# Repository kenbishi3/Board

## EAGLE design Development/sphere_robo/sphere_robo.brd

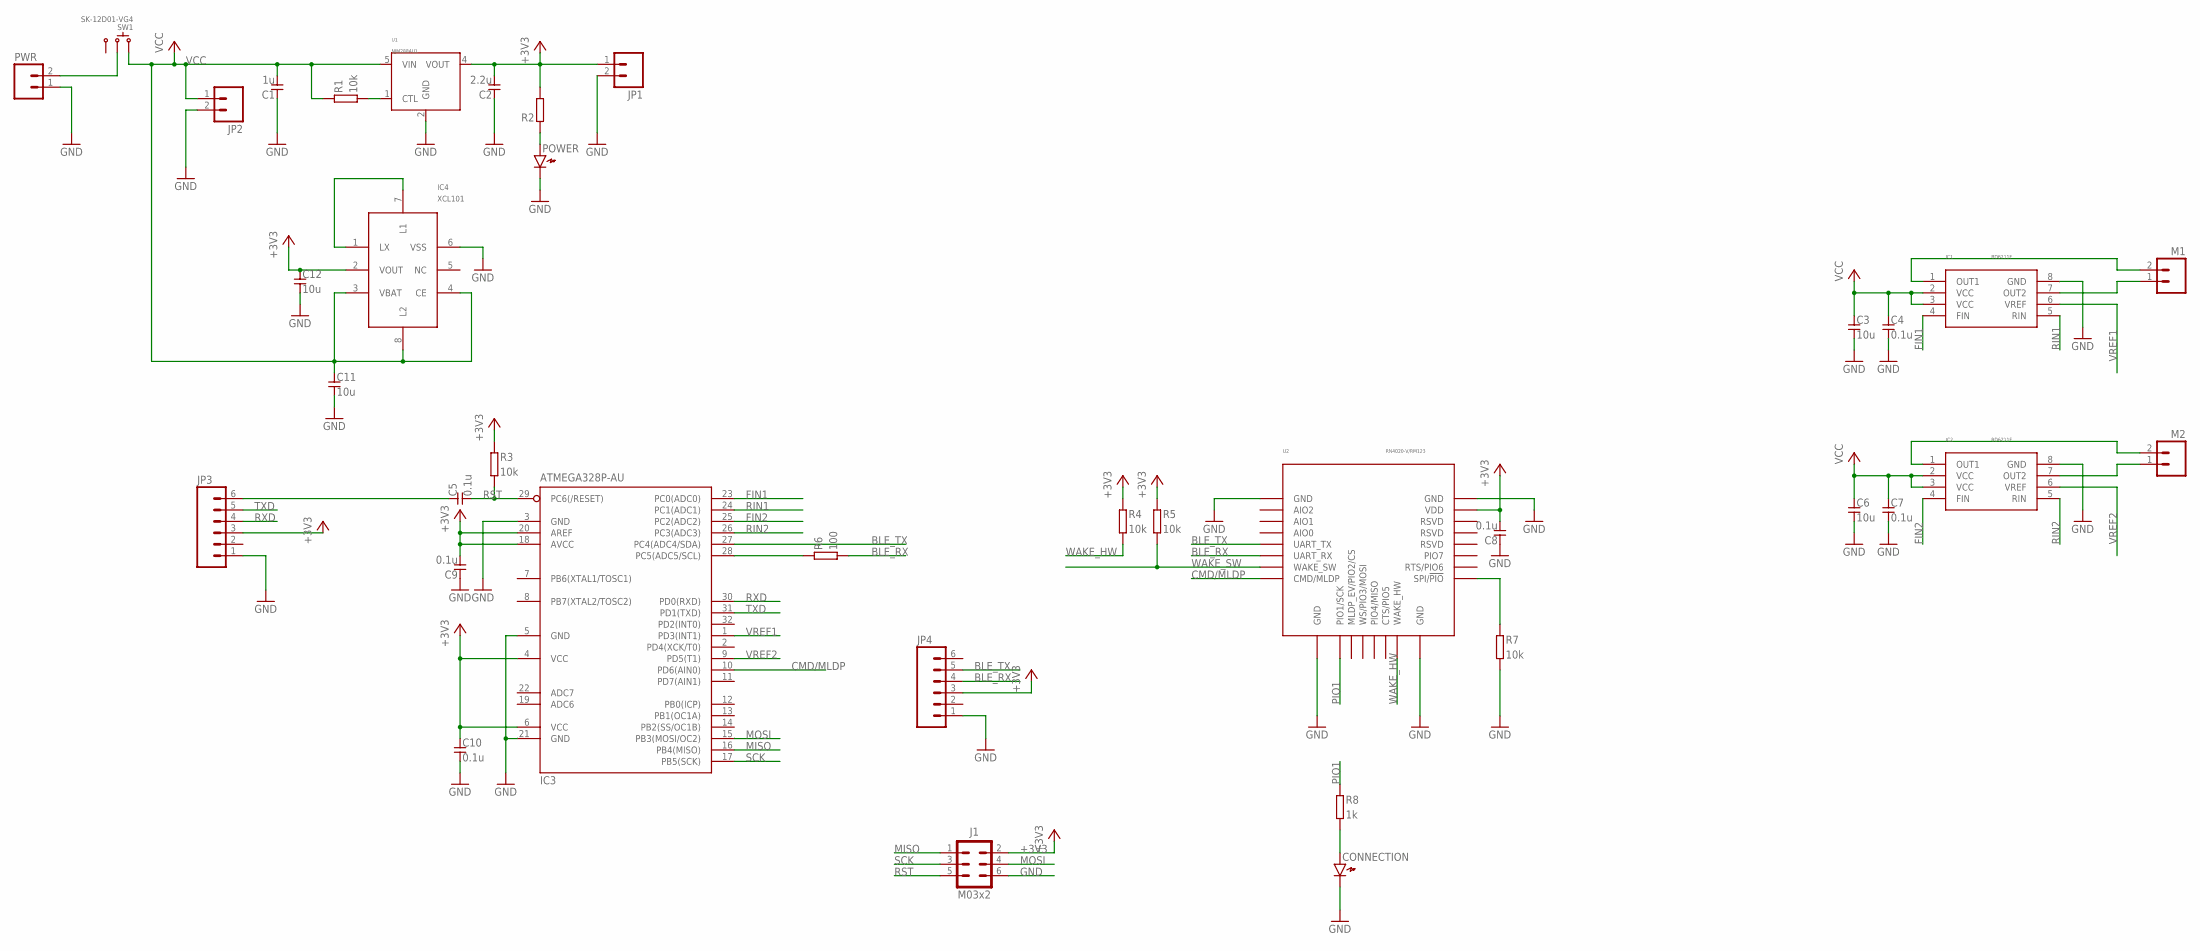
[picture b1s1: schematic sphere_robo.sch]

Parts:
C1: 1u; SMD1608_REDUCED
C2: 2.2u; SMD1608_REDUCED
C3, C6, C11, C12: 10u; SMD2012_REDUCED
C4, C5, C7, C8, C9, C10: 0.1u; SMD1608_REDUCED
CONNECTION: LED1608_REDUCED
IC1, IC2: BD6211F; SOP-8
IC3: ATMEGA328P-AU; TQFP32-08
IC4: XCL101; CL-2025
J1: M03X2STD; 2X03
JP1, JP2: M02NOSILK; 1X02-NOSILK
JP3, JP4: M06NOSILK; 1X06-NOSILK
M1, M2: M02NOSILK; 1X02-NOSILK
POWER: LED1608_REDUCED
PWR: M02NOSILK; 1X02-NOSILK
R1, R3, R4, R5, R7: 10k; SMD1608_REDUCED
R2: RESISTOR1608_REDUCED; SMD1608_REDUCED
R6: 100; SMD1608_REDUCED
R8: 1k; SMD1608_REDUCED
SW1: SK-12D01-VG4
U1: NJM2884U1; SOT-89-5
U2: RN4020-V/RM123; RN4020

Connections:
+3V3: C2.2, C8.2, C9.2, C10.1, C12.1, IC3.4 (VCC), IC3.6 (VCC), IC3.18 (AVCC), IC3.20 (AREF), IC4.2 (VOUT), J1.2, JP1.1, JP3.3, JP4.3, R2.2, R3.1, R4.1, R5.1, U1.4 (VOUT), U2.23 (VDD)
BLE_RX: JP4.4, R6.2, U2.6 (UART_RX)
BLE_TX: IC3.27 (PC4(ADC4/SDA)), JP4.5, U2.5 (UART_TX)
CMD/MLDP: IC3.10 (PD6(AIN0)), U2.8 (CMD/MLDP)
FIN1: IC1.4 (FIN), IC3.23 (PC0(ADC0))
FIN2: IC2.4 (FIN), IC3.25 (PC2(ADC2))
GND: C1.1, C2.1, C3.2, C4.2, C6.2, C7.2, C8.1, C9.1, C10.2, C11.2, C12.2, CONNECTION.K, IC1.8 (GND), IC2.8 (GND), IC3.3 (GND), IC3.5 (GND), IC3.21 (GND), IC4.6 (VSS), J1.6, JP1.2, JP2.2, JP3.1, JP4.1, POWER.K, PWR.1, R7.2, U1.2 (GND), U2.1 (GND), U2.9 (GND), U2.16 (GND), U2.24 (GND)
MISO: IC3.16 (PB4(MISO)), J1.1
MOSI: IC3.15 (PB3(MOSI/OC2)), J1.4
unnamed: C5.1, JP3.6
unnamed: CONNECTION.A, R8.2
unnamed: IC3.28 (PC5(ADC5/SCL)), R6.1
unnamed: R7.1, U2.17 (SPI/!PIO)
unnamed: PWR.2, SW1.2
unnamed: R1.2, U1.1 (CTL)
unnamed: IC4.1 (LX), IC4.7 (L1)
unnamed: POWER.A, R2.1
unnamed: IC2.1 (OUT1), M2.2
unnamed: IC2.7 (OUT2), M2.1
unnamed: IC1.1 (OUT1), M1.2
unnamed: IC1.7 (OUT2), M1.1
PIO1: R8.1, U2.10 (PIO1/SCK)
RIN1: IC1.5 (RIN), IC3.24 (PC1(ADC1))
RIN2: IC2.5 (RIN), IC3.26 (PC3(ADC3))
RST: C5.2, IC3.29 (PC6(/RESET)), J1.5, R3.2
RXD: IC3.30 (PD0(RXD)), JP3.4
SCK: IC3.17 (PB5(SCK)), J1.3
TXD: IC3.31 (PD1(TXD)), JP3.5
VCC: C1.2, C3.1, C4.1, C6.1, C7.1, C11.1, IC1.2 (VCC), IC1.3 (VCC), IC2.2 (VCC), IC2.3 (VCC), IC4.3 (VBAT), IC4.4 (CE), IC4.8 (L2), JP2.1, R1.1, SW1.1, U1.5 (VIN)
VREF1: IC1.6 (VREF), IC3.1 (PD3(INT1))
VREF2: IC2.6 (VREF), IC3.9 (PD5(T1))
WAKE_HW: R4.2, U2.15 (WAKE_HW)
WAKE_SW: R5.2, U2.7 (WAKE_SW)

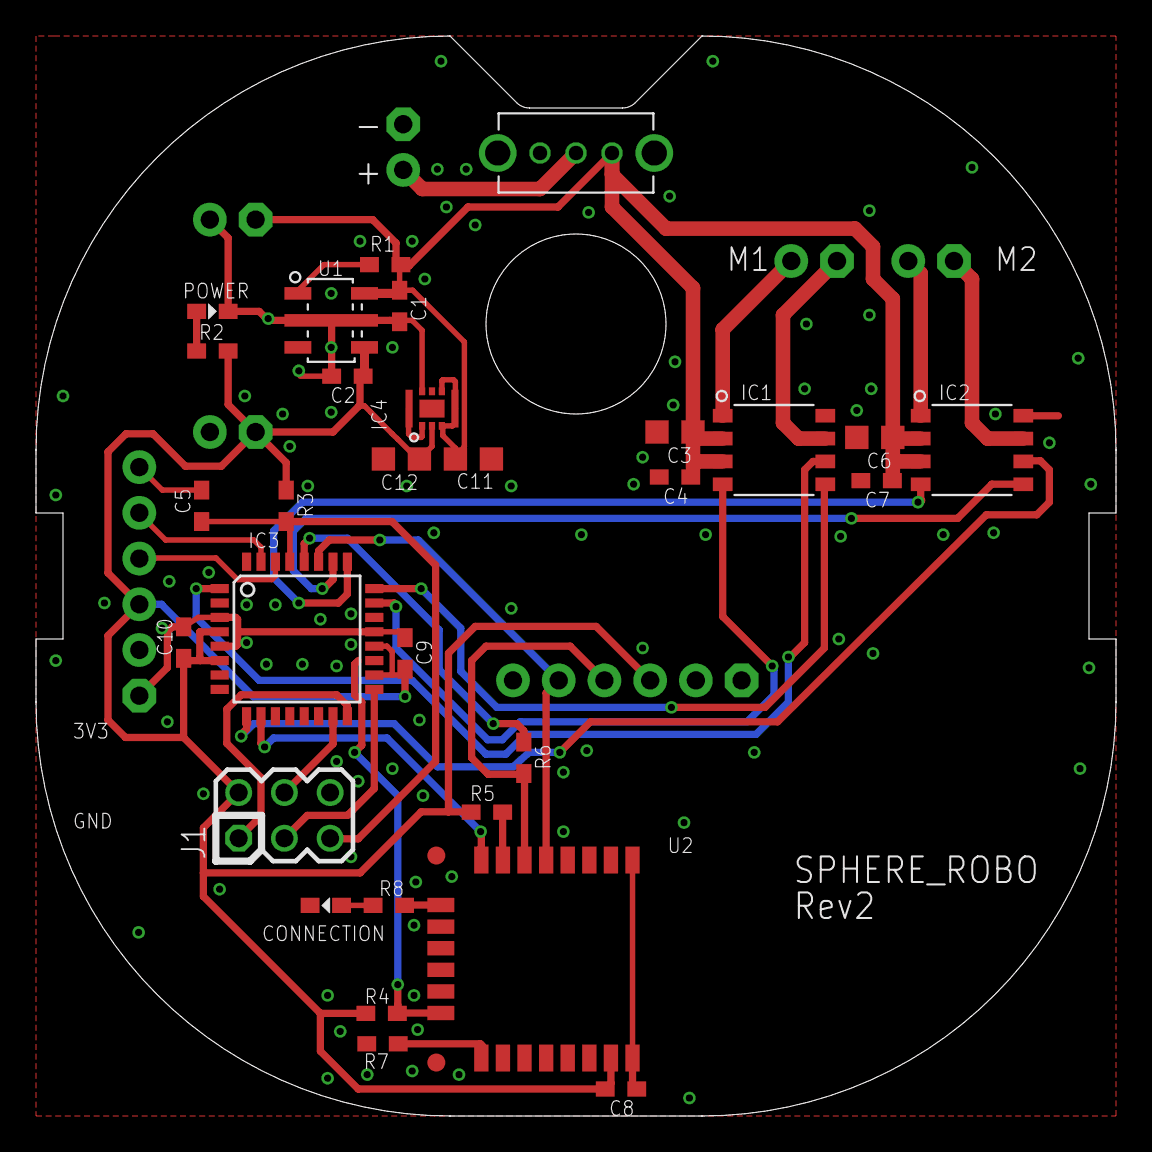
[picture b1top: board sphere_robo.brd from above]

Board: 2 copper layers, 60.0 x 60.0 mm, 37 parts (0 on the bottom side), 33 nets.

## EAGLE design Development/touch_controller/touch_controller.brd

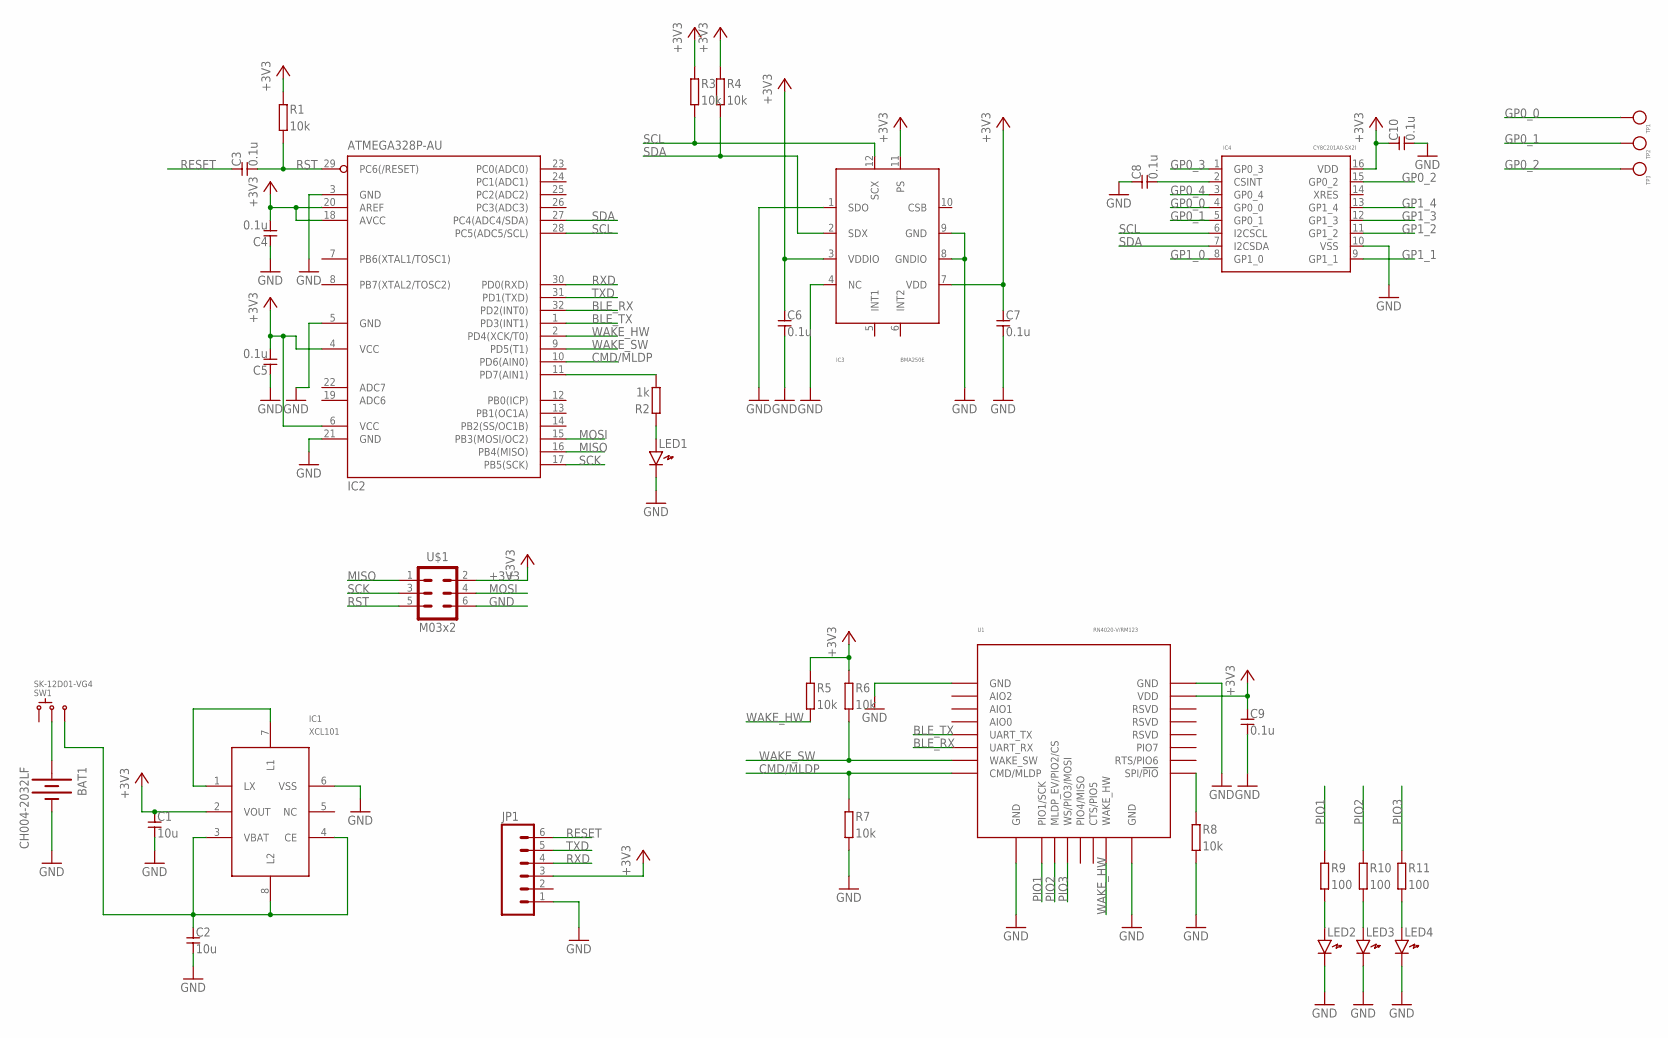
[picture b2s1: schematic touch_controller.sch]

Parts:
BAT1: CH004-2032LF
C1, C2: 10u; SMD2012_REDUCED
C3, C4, C5, C6, C7, C8, C9, C10: 0.1u; SMD1608_REDUCED
IC1: XCL101; CL-2025
IC2: ATMEGA328P-AU; TQFP32-08
IC3: BMA250E; LGA-12
IC4: CY8C201A0-SX2I; SOIC-16
JP1: M06NOSILK; 1X06-NOSILK
LED1, LED2, LED3, LED4: LED1608_REDUCED
R1, R3, R4, R5, R6, R7, R8: 10k; SMD1608_REDUCED
R2: 1k; SMD1608_REDUCED
R9, R10, R11: 100; SMD1608_REDUCED
SW1: SK-12D01-VG4
TP1, TP2, TP3: HT-0720-10
U1: RN4020-V/RM123; RN4020
U$1: M03X2STD; 2X03

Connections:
+3V3: C1.1, C4.2, C5.2, C6.1, C7.1, C9.1, C10.1, IC1.2 (VOUT), IC2.4 (VCC), IC2.6 (VCC), IC2.18 (AVCC), IC2.20 (AREF), IC3.3 (VDDIO), IC3.7 (VDD), IC3.11 (PS), IC4.16 (VDD), JP1.3, R1.1, R3.1, R4.1, R5.1, R6.1, U1.23 (VDD), U$1.2
BLE_RX: IC2.32 (PD2(INT0)), U1.6 (UART_RX)
BLE_TX: IC2.1 (PD3(INT1)), U1.5 (UART_TX)
CMD/MLDP: IC2.10 (PD6(AIN0)), R7.1, U1.8 (CMD/MLDP)
GND: BAT1.-, C1.2, C2.2, C4.1, C5.1, C6.2, C7.2, C8.1, C9.2, C10.2, IC1.6 (VSS), IC2.3 (GND), IC2.5 (GND), IC2.21 (GND), IC3.1 (SDO), IC3.4 (NC), IC3.8 (GNDIO), IC3.9 (GND), IC4.10 (VSS), JP1.1, LED1.K, LED2.K, LED3.K, LED4.K, R7.2, R8.2, U1.1 (GND), U1.9 (GND), U1.16 (GND), U1.24 (GND), U$1.6
GP0_0: IC4.4 (GP0_0), TP1.P$1
GP0_1: IC4.5 (GP0_1), TP2.P$1
GP0_2: IC4.15 (GP0_2), TP3.P$1
GP0_3: IC4.1 (GP0_3)
GP0_4: IC4.3 (GP0_4)
GP1_0: IC4.8 (GP1_0)
GP1_1: IC4.9 (GP1_1)
GP1_2: IC4.11 (GP1_2)
GP1_3: IC4.12 (GP1_3)
GP1_4: IC4.13 (GP1_4)
MISO: IC2.16 (PB4(MISO)), U$1.1
MOSI: IC2.15 (PB3(MOSI/OC2)), U$1.4
unnamed: BAT1.+, SW1.2
unnamed: C8.2, IC4.2 (CSINT)
unnamed: R8.1, U1.17 (SPI/!PIO)
unnamed: IC2.11 (PD7(AIN1)), R2.2
unnamed: LED2.A, R9.2
unnamed: LED3.A, R10.2
unnamed: LED4.A, R11.2
unnamed: LED1.A, R2.1
unnamed: C2.1, IC1.3 (VBAT), IC1.4 (CE), IC1.8 (L2), SW1.3
unnamed: IC1.1 (LX), IC1.7 (L1)
PIO1: R9.1, U1.10 (PIO1/SCK)
PIO2: R10.1, U1.11 (MLDP_EV/PIO2/CS)
PIO3: R11.1, U1.12 (WS/PIO3/MOSI)
RESET: C3.1, JP1.6
RST: C3.2, IC2.29 (PC6(/RESET)), R1.2, U$1.5
RXD: IC2.30 (PD0(RXD)), JP1.4
SCK: IC2.17 (PB5(SCK)), U$1.3
SCL: IC2.28 (PC5(ADC5/SCL)), IC3.12 (SCX), IC4.6 (I2CSCL), R3.2
SDA: IC2.27 (PC4(ADC4/SDA)), IC3.2 (SDX), IC4.7 (I2CSDA), R4.2
TXD: IC2.31 (PD1(TXD)), JP1.5
WAKE_HW: IC2.2 (PD4(XCK/T0)), R5.2, U1.15 (WAKE_HW)
WAKE_SW: IC2.9 (PD5(T1)), R6.2, U1.7 (WAKE_SW)

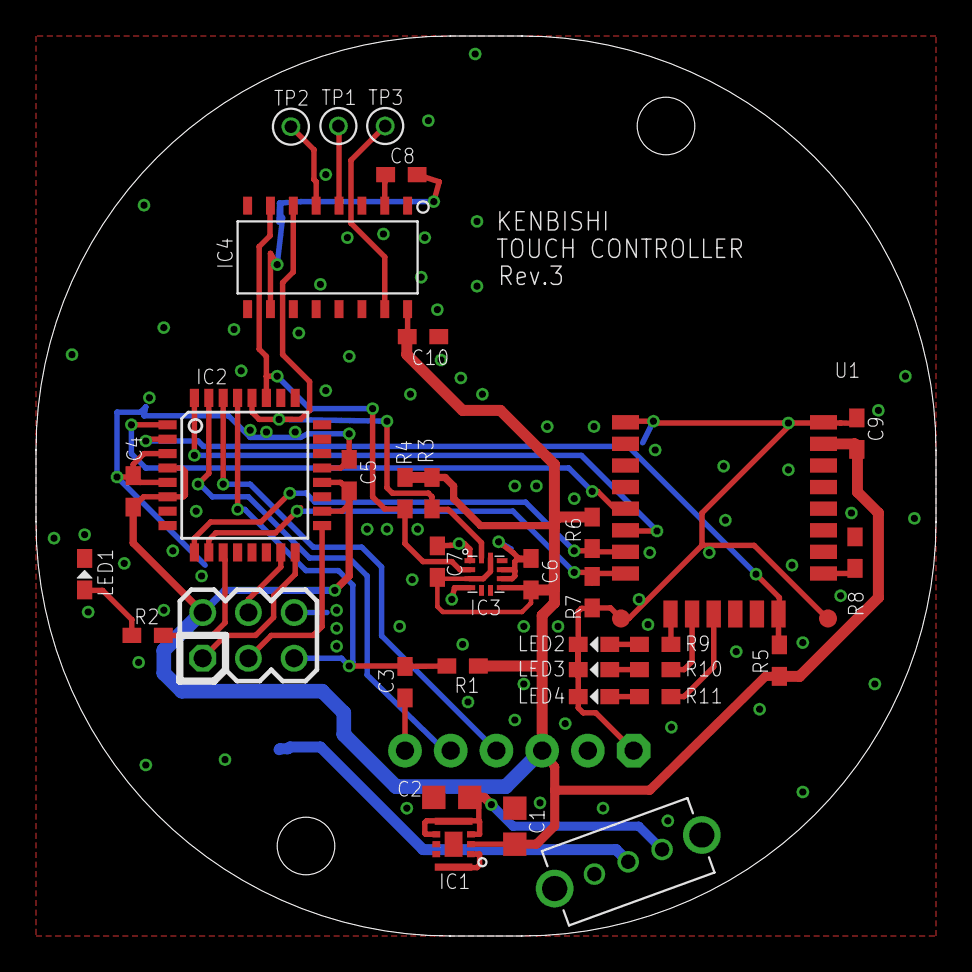
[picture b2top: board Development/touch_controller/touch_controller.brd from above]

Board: 2 copper layers, 50.0 x 50.0 mm, 37 parts (1 on the bottom side), 32 nets.

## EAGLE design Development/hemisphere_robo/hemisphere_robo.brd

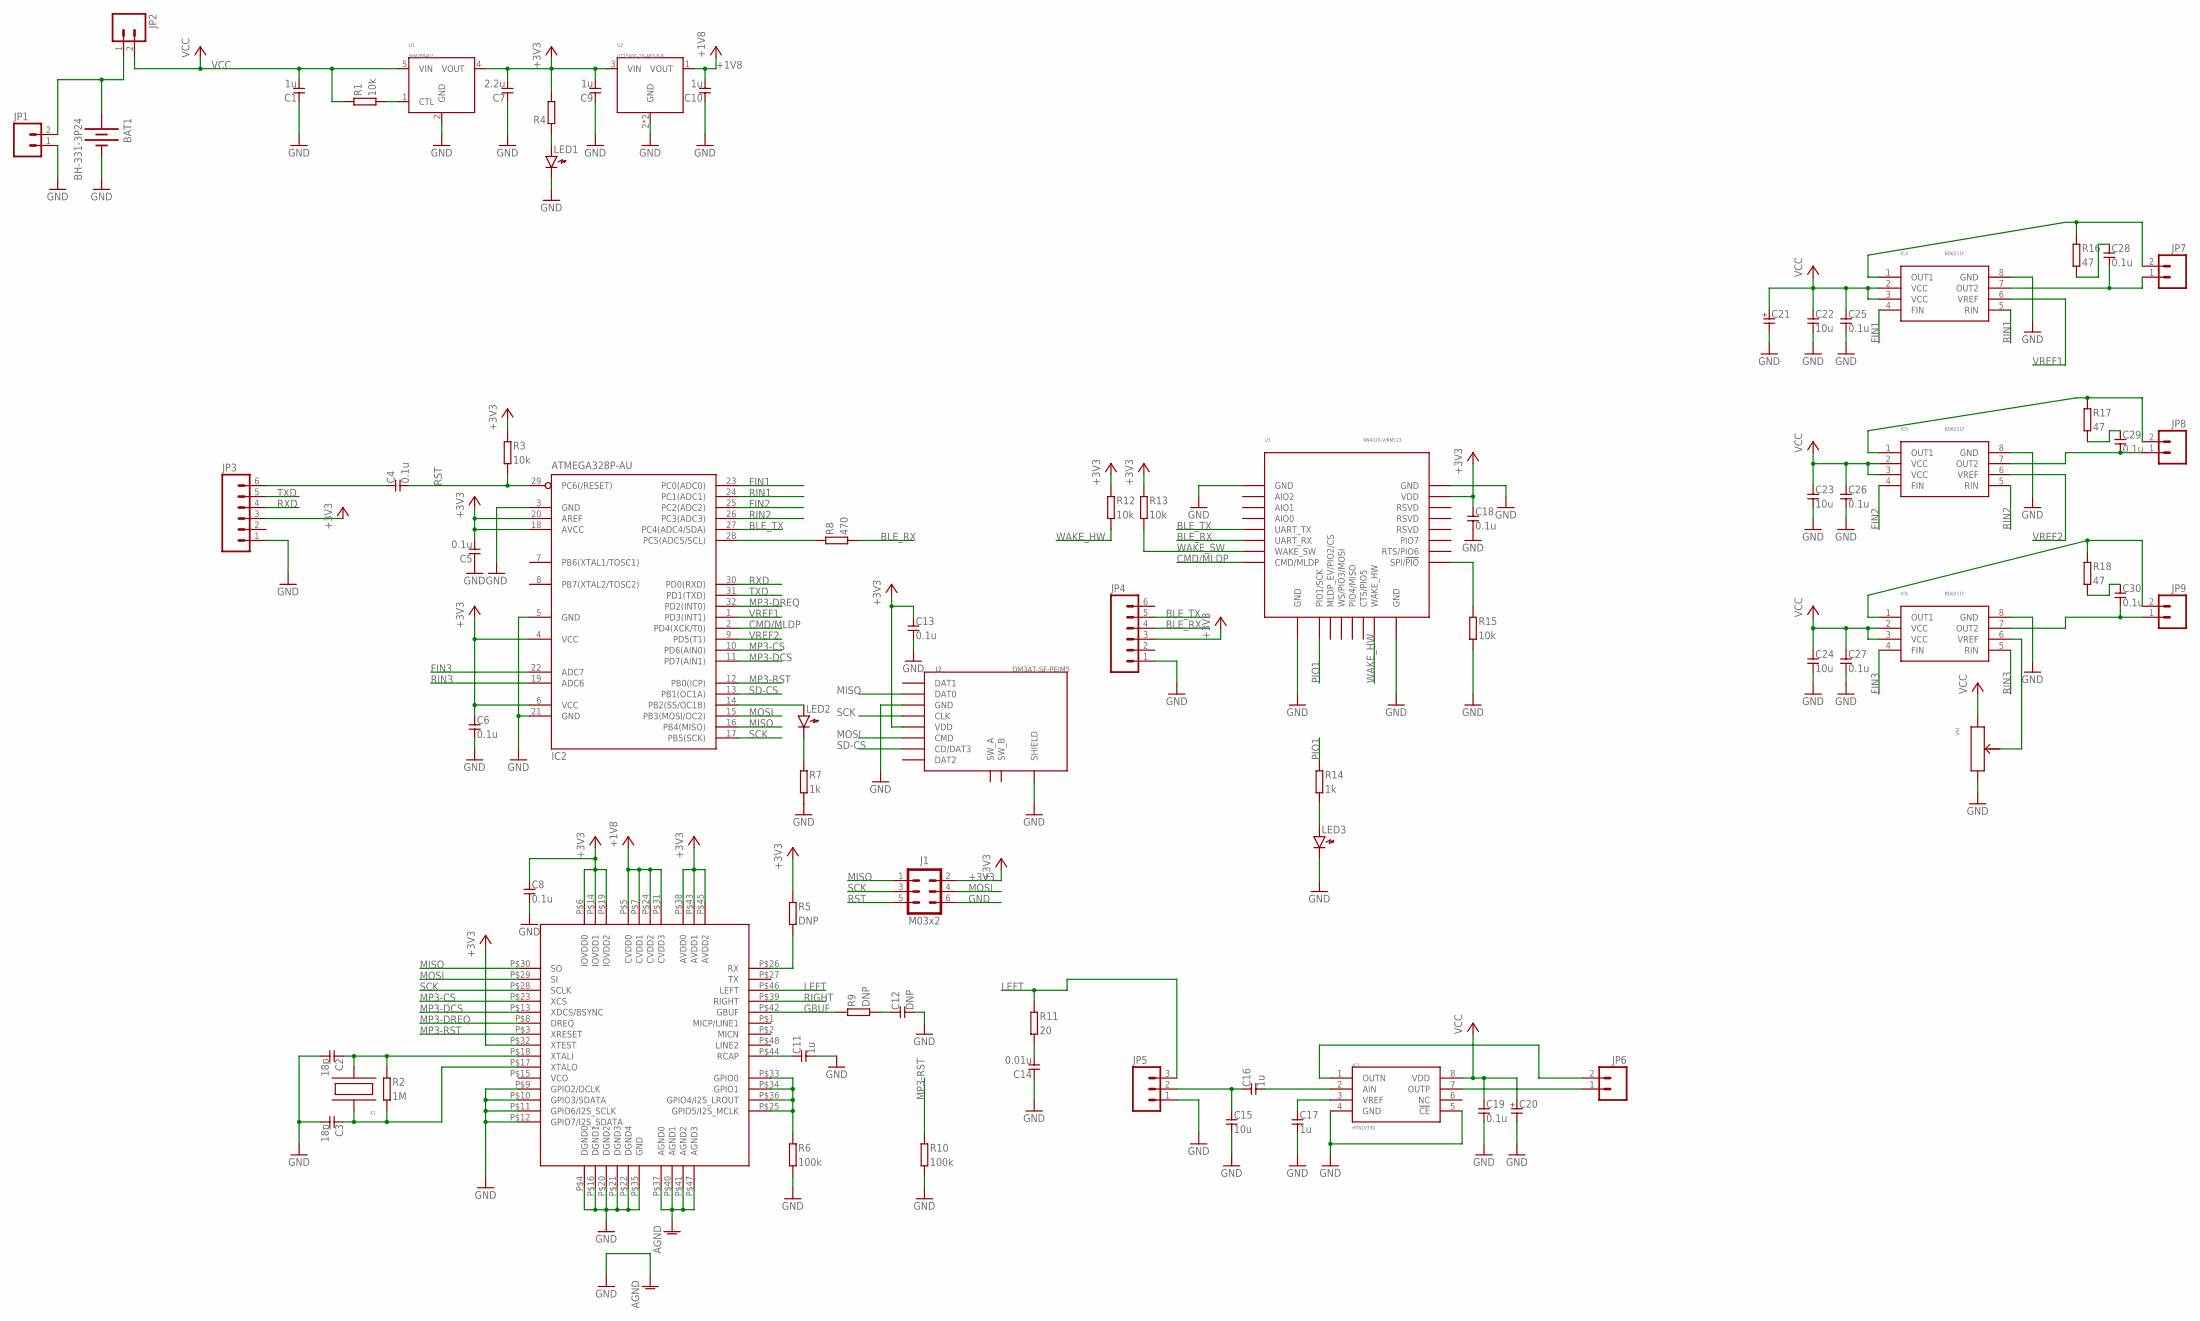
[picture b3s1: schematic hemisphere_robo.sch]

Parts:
BAT1: BH-331-3P24
C1, C9, C10, C11, C16, C17: 1u; SMD1608_REDUCED
C2, C3: 18p; SMD1608_REDUCED
C4, C5, C6, C8, C13, C18, C19, C25, C26, C27, C28, C29, C30: 0.1u; SMD1608_REDUCED
C7: 2.2u; SMD1608_REDUCED
C12: DNP; SMD1608_REDUCED
C14: 0.01u; SMD1608_REDUCED
C15, C22, C23, C24: 10u; SMD2012_REDUCED
C20, C21: CAPACITOR-POLPANASONIC_D; PANASONIC_D
IC1: VS1053B; LQFP48
IC2: ATMEGA328P-AU; TQFP32-08
IC3: HT82V739; DIP8
IC4, IC5, IC6: BD6211F; SOP-8
J1: M03X2STD; 2X03
J2: DM3AT-SF-PEJM5
JP1, JP2, JP6, JP7, JP8, JP9: M02NOSILK; 1X02-NOSILK
JP3, JP4: M06NOSILK; 1X06-NOSILK
JP5: M03NOSILK; 1X03-NOSILK
LED1, LED2, LED3: LED1608_REDUCED
R1, R3, R12, R13, R15: 10k; SMD1608_REDUCED
R2: 1M; SMD1608_REDUCED
R4: RESISTOR1608_REDUCED; SMD1608_REDUCED
R5, R9: DNP; SMD1608_REDUCED
R6, R10: 100k; SMD1608_REDUCED
R7, R14: 1k; SMD1608_REDUCED
R8: 470; SMD1608_REDUCED
R11: 20; SMD1608_REDUCED
R16, R17, R18: 47; SMD1608_REDUCED
U1: NJM2884U1; SOT-89-5
U2: UT7500G-18-AB3-B-R; SOT-89
U3: RN4020-V/RM123; RN4020
VR1: VR; 3362P
X1: ABM2

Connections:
+1V8: C10.2, IC1.P$5 (CVDD0), IC1.P$7 (CVDD1), IC1.P$24 (CVDD2), IC1.P$31 (CVDD3), U2.1 (VOUT)
+3V3: C5.2, C6.1, C7.2, C8.1, C9.2, C13.1, C18.1, IC1.P$6 (IOVDD0), IC1.P$14 (IOVDD1), IC1.P$19 (IOVDD2), IC1.P$32 (XTEST), IC1.P$38 (AVDD0), IC1.P$43 (AVDD1), IC1.P$45 (AVDD2), IC2.4 (VCC), IC2.6 (VCC), IC2.18 (AVCC), IC2.20 (AREF), J1.2, J2.4(VDD) (VDD), JP3.3, JP4.3, R3.1, R4.2, R5.1, R12.1, R13.1, U1.4 (VOUT), U2.3 (VIN), U3.23 (VDD)
BLE_RX: JP4.4, R8.2, U3.6 (UART_RX)
BLE_TX: IC2.27 (PC4(ADC4/SDA)), JP4.5, U3.5 (UART_TX)
CMD/MLDP: IC2.2 (PD4(XCK/T0)), U3.8 (CMD/MLDP)
FIN1: IC2.23 (PC0(ADC0)), IC4.4 (FIN)
FIN2: IC2.25 (PC2(ADC2)), IC5.4 (FIN)
FIN3: IC2.22 (ADC7), IC6.4 (FIN)
GBUF: IC1.P$42 (GBUF), R9.1
GND: BAT1.-, C1.1, C2.2, C3.2, C5.1, C6.2, C7.1, C8.2, C9.1, C10.1, C11.2, C12.2, C13.2, C14.1, C15.2, C17.2, C18.2, C19.2, C20.-, C21.-, C22.2, C23.2, C24.2, C25.2, C26.2, C27.2, IC1.P$4 (DGND0), IC1.P$9 (GPIO2/DCLK), IC1.P$10 (GPIO3/SDATA), IC1.P$11 (GPIO6/I2S_SCLK), IC1.P$12 (GPIO7/I2S_SDATA), IC1.P$16 (DGND1), IC1.P$20 (DGND2), IC1.P$21 (DGND3), IC1.P$22 (DGND4), IC1.P$35 (GND), IC1.P$37 (AGND0), IC1.P$40 (AGND1), IC1.P$41 (AGND2), IC1.P$47 (AGND3), IC2.3 (GND), IC2.5 (GND), IC2.21 (GND), IC3.4 (GND), IC3.5 (!CE), IC4.8 (GND), IC5.8 (GND), IC6.8 (GND), J1.6, J2.6(GND) (GND), J2.SHIELD@1 (SHIELD), J2.SHIELD@2 (SHIELD), J2.SHIELD@3 (SHIELD), J2.SHIELD@4 (SHIELD), JP1.1, JP3.1, JP4.1, JP5.1, LED1.K, LED3.K, R6.2, R7.2, R10.2, R15.2, U1.2 (GND), U2.2 (GND), U2.4 (GND), U3.1 (GND), U3.9 (GND), U3.16 (GND), U3.24 (GND), VR1.3
LEFT: IC1.P$46 (LEFT), JP5.3, R11.1
MISO: IC1.P$30 (SO), IC2.16 (PB4(MISO)), J1.1, J2.7(DAT0) (DAT0)
MOSI: IC1.P$29 (SI), IC2.15 (PB3(MOSI/OC2)), J1.4, J2.3(CMD) (CMD)
MP3-CS: IC1.P$23 (XCS), IC2.10 (PD6(AIN0))
MP3-DCS: IC1.P$13 (XDCS/BSYNC), IC2.11 (PD7(AIN1))
MP3-DREQ: IC1.P$8 (DREQ), IC2.32 (PD2(INT0))
MP3-RST: IC1.P$3 (XRESET), IC2.12 (PB0(ICP)), R10.1
unnamed: IC2.14 (PB2(SS/OC1B)), LED2.A
unnamed: C4.1, JP3.6
unnamed: LED3.A, R14.2
unnamed: IC2.28 (PC5(ADC5/SCL)), R8.1
unnamed: IC6.1 (OUT1), JP9.2, R18.1
unnamed: IC1.P$25 (GPIO5/I2S_MCLK), IC1.P$33 (GPIO0), IC1.P$34 (GPIO1), IC1.P$36 (GPIO4/I2S_LROUT), R6.1
unnamed: C11.1, IC1.P$44 (RCAP)
unnamed: R15.1, U3.17 (SPI/!PIO)
unnamed: IC1.P$26 (RX), R5.2
unnamed: BAT1.+, JP1.2, JP2.1
unnamed: IC3.7 (OUTP), JP6.1
unnamed: C2.1, IC1.P$18 (XTALI), R2.1, X1.2
unnamed: C14.2, R11.2
unnamed: C12.1, R9.2
unnamed: R1.2, U1.1 (CTL)
unnamed: C3.1, IC1.P$17 (XTALO), R2.2, X1.1
unnamed: C30.2, IC6.7 (OUT2), JP9.1
unnamed: IC6.6 (VREF), VR1.2
unnamed: C17.1, IC3.3 (VREF)
unnamed: C16.2, IC3.2 (AIN)
unnamed: C15.1, C16.1, JP5.2
unnamed: C28.1, R16.2
unnamed: C29.1, R17.2
unnamed: C30.1, R18.2
unnamed: IC3.1 (OUTN), JP6.2
unnamed: LED1.A, R4.1
unnamed: IC5.1 (OUT1), JP8.2, R17.1
unnamed: C29.2, IC5.7 (OUT2), JP8.1
unnamed: IC4.1 (OUT1), JP7.2, R16.1
unnamed: C28.2, IC4.7 (OUT2), JP7.1
PIO1: R14.1, U3.10 (PIO1/SCK)
RIGHT: IC1.P$39 (RIGHT)
RIN1: IC2.24 (PC1(ADC1)), IC4.5 (RIN)
RIN2: IC2.26 (PC3(ADC3)), IC5.5 (RIN)
RIN3: IC2.19 (ADC6), IC6.5 (RIN)
RST: C4.2, IC2.29 (PC6(/RESET)), J1.5, R3.2
RXD: IC2.30 (PD0(RXD)), JP3.4
SCK: IC1.P$28 (SCLK), IC2.17 (PB5(SCK)), J1.3, J2.5(CLK) (CLK)
SD-CS: IC2.13 (PB1(OC1A)), J2.2(CD/DAT3) (CD/DAT3)
SHUTDOWN: LED2.K, R7.1
TXD: IC2.31 (PD1(TXD)), JP3.5
VCC: C1.2, C19.1, C20.+, C21.+, C22.1, C23.1, C24.1, C25.1, C26.1, C27.1, IC3.8 (VDD), IC4.2 (VCC), IC4.3 (VCC), IC5.2 (VCC), IC5.3 (VCC), IC6.2 (VCC), IC6.3 (VCC), JP2.2, R1.1, U1.5 (VIN), VR1.1
VREF1: IC2.1 (PD3(INT1)), IC4.6 (VREF)
VREF2: IC2.9 (PD5(T1)), IC5.6 (VREF)
WAKE_HW: R12.2, U3.15 (WAKE_HW)
WAKE_SW: R13.2, U3.7 (WAKE_SW)

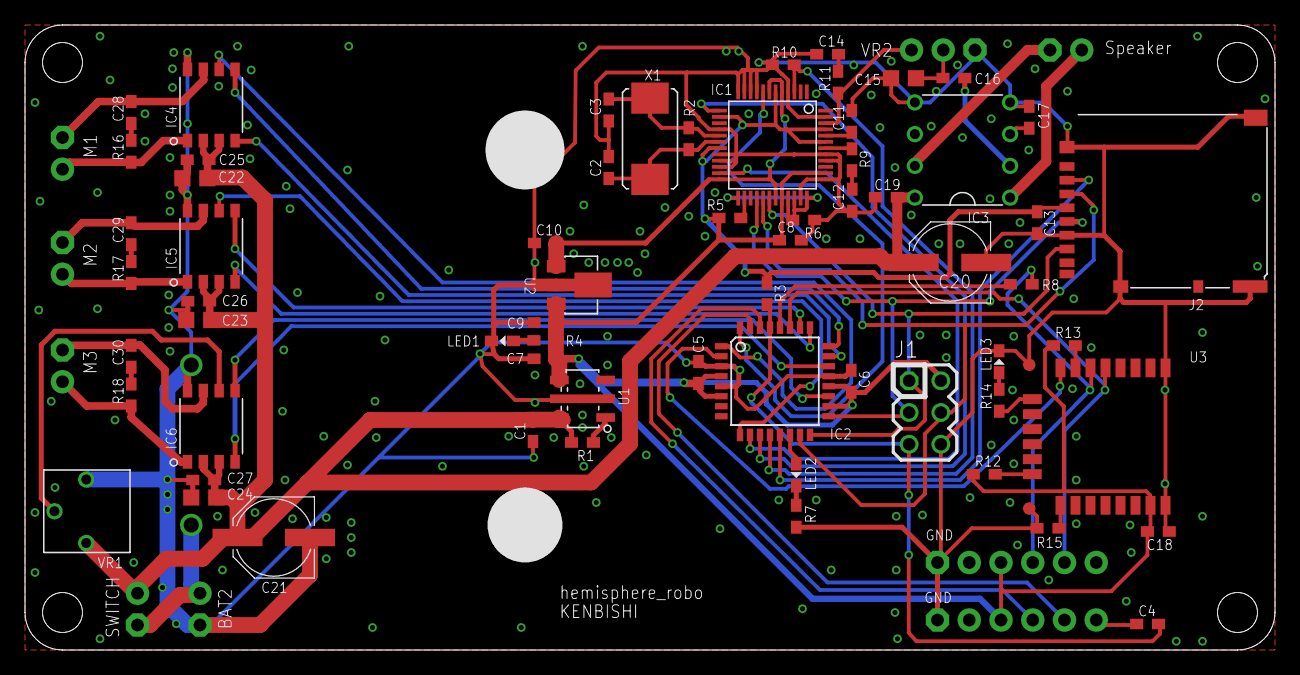
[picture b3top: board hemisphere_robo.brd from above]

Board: 2 copper layers, 100.0 x 50.0 mm, 74 parts (1 on the bottom side), 62 nets.

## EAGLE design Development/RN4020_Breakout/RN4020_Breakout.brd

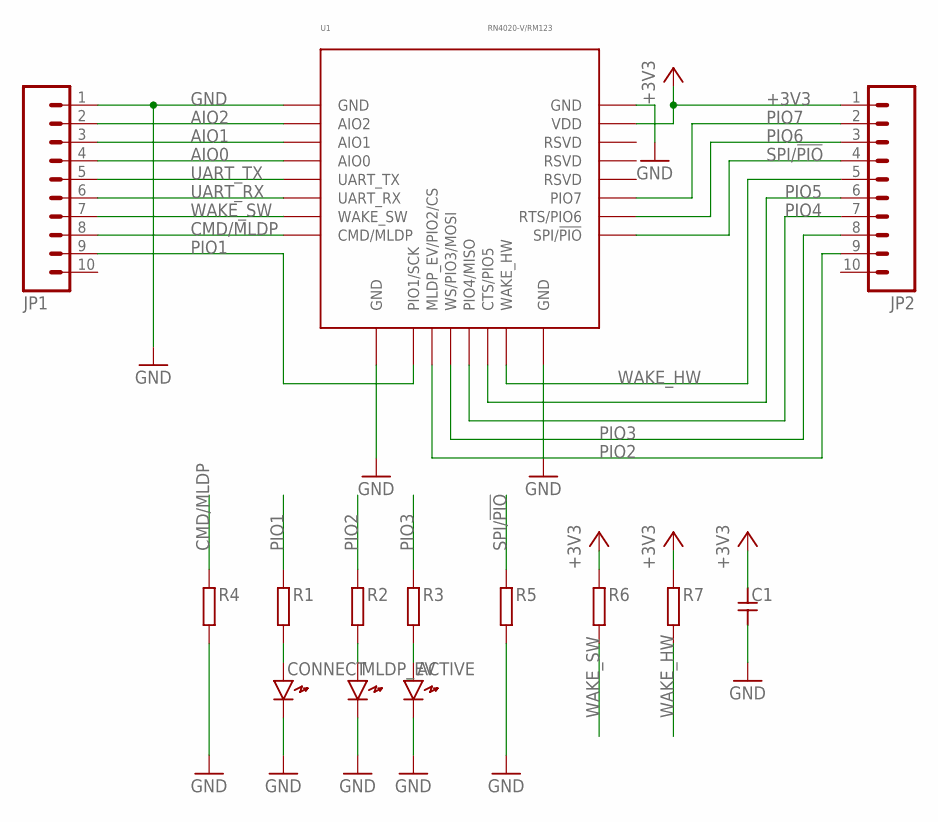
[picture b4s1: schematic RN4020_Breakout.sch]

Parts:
ACTIVE: LED1608_REDUCED
C1: CAPACITOR1608_REDUCED; SMD1608_REDUCED
CONNECT: LED1608_REDUCED
JP1, JP2: M10NOSILK; 1X10-NOSILK
MLDP_EV: LED1608_REDUCED
R1, R2, R3, R4, R5, R6, R7: RESISTOR1608_REDUCED; SMD1608_REDUCED
U1: RN4020-V/RM123; RN4020

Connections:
+3V3: C1.1, JP2.1, R6.1, R7.1, U1.23 (VDD)
AIO0: JP1.4, U1.4 (AIO0)
AIO1: JP1.3, U1.3 (AIO1)
AIO2: JP1.2, U1.2 (AIO2)
CMD/MLDP: JP1.8, R4.1, U1.8 (CMD/MLDP)
GND: ACTIVE.K, C1.2, CONNECT.K, JP1.1, MLDP_EV.K, R4.2, R5.2, U1.1 (GND), U1.9 (GND), U1.16 (GND), U1.24 (GND)
unnamed: CONNECT.A, R1.2
unnamed: MLDP_EV.A, R2.2
unnamed: ACTIVE.A, R3.2
PIO1: JP1.9, R1.1, U1.10 (PIO1/SCK)
PIO2: JP2.9, R2.1, U1.11 (MLDP_EV/PIO2/CS)
PIO3: JP2.8, R3.1, U1.12 (WS/PIO3/MOSI)
PIO4: JP2.7, U1.13 (PIO4/MISO)
PIO5: JP2.6, U1.14 (CTS/PIO5)
PIO6: JP2.3, U1.18 (RTS/PIO6)
PIO7: JP2.2, U1.19 (PIO7)
SPI/!PIO: JP2.4, R5.1, U1.17 (SPI/!PIO)
UART_RX: JP1.6, U1.6 (UART_RX)
UART_TX: JP1.5, U1.5 (UART_TX)
WAKE_HW: JP2.5, R7.2, U1.15 (WAKE_HW)
WAKE_SW: JP1.7, R6.2, U1.7 (WAKE_SW)

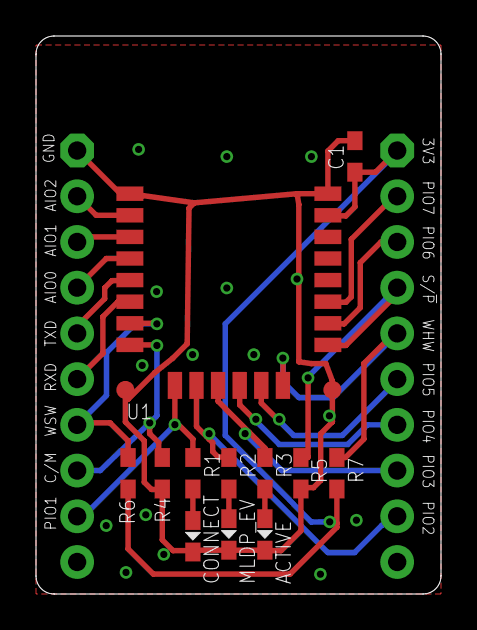
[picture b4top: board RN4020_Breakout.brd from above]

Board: 2 copper layers, 22.5 x 31.0 mm, 14 parts (0 on the bottom side), 21 nets.

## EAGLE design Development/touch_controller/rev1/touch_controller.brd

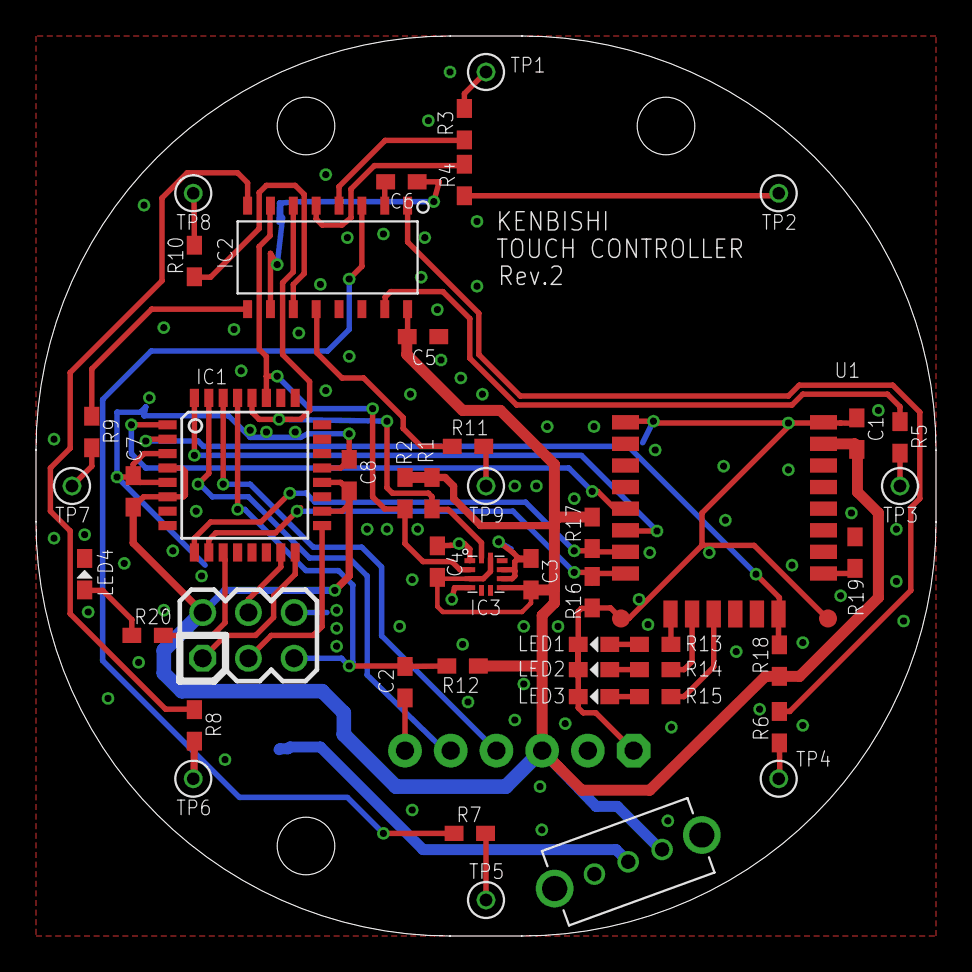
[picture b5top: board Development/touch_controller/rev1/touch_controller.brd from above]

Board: 2 copper layers, 50.0 x 50.0 mm, 49 parts (1 on the bottom side), 45 nets.

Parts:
BAT1: CH004-2032LF
C1, C2, C3, C4, C5, C6, C7, C8: 0.1u; SMD1608_REDUCED
IC1: ATMEGA328P-AU; TQFP32-08
IC2: CY8C201A0-SX2I; SOIC-16
IC3: BMA250E; LGA-12
JP1: 1X06-NOSILK
LED1, LED2, LED3, LED4: LED1608_REDUCED
R1, R2, R12, R16, R17, R18, R19: 10k; SMD1608_REDUCED
R3, R4, R5, R6, R7, R8, R9, R10, R11: 0; SMD1608_REDUCED
R13, R14, R15: 100; SMD1608_REDUCED
R20: 1k; SMD1608_REDUCED
SW1: SK-12D01-VG4
TP1, TP2, TP3, TP4, TP5, TP6, TP7, TP8, TP9: HT-0720-10
U1: RN4020-V/RM123; RN4020
U$1: M03X2STD; 2X03

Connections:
+3V3: C1.1, C3.1, C4.1, C5.1, C7.2, C8.2, IC1.4, IC1.6, IC1.18, IC1.20, IC2.16, IC3.3, IC3.7, IC3.11, JP1.3, R1.1, R2.1, R12.1, R17.1, R18.1, SW1.3, U1.23, U$1.2
BLE_RX: IC1.32, U1.6
BLE_TX: IC1.1, U1.5
CMD/MLDP: IC1.10, R16.1, U1.8
GND: BAT1.-, C1.2, C3.2, C4.2, C5.2, C6.1, C7.1, C8.1, IC1.3, IC1.5, IC1.21, IC2.10, IC3.1, IC3.4, IC3.8, IC3.9, JP1.1, LED1.K, LED2.K, LED3.K, LED4.K, R16.2, R19.2, U1.1, U1.9, U1.16, U1.24, U$1.6
GP0_0: IC2.4, R3.1
GP0_1: IC2.5, R4.1
GP0_2: IC2.15, R5.1
GP0_3: IC2.1, R6.1
GP0_4: IC2.3, R7.1
GP1_0: IC2.8, R8.1
GP1_1: IC2.9, R9.1
GP1_2: IC2.11, R10.1
GP1_3: IC2.12, R11.1
MISO: IC1.16, U$1.1
MOSI: IC1.15, U$1.4
unnamed: BAT1.+, SW1.2
unnamed: C6.2, IC2.2
unnamed: R3.2, TP1.P$1
unnamed: R4.2, TP2.P$1
unnamed: R5.2, TP3.P$1
unnamed: R6.2, TP4.P$1
unnamed: R7.2, TP5.P$1
unnamed: R8.2, TP6.P$1
unnamed: R9.2, TP7.P$1
unnamed: R10.2, TP8.P$1
unnamed: R11.2, TP9.P$1
unnamed: R19.1, U1.17
unnamed: IC1.11, R20.2
unnamed: LED1.A, R13.2
unnamed: LED2.A, R14.2
unnamed: LED3.A, R15.2
unnamed: LED4.A, R20.1
PIO1: R13.1, U1.10
PIO2: R14.1, U1.11
PIO3: R15.1, U1.12
RESET: C2.1, JP1.6
RST: C2.2, IC1.29, R12.2, U$1.5
RXD: IC1.30, JP1.4
SCK: IC1.17, U$1.3
SCL: IC1.28, IC2.6, IC3.12, R1.2
SDA: IC1.27, IC2.7, IC3.2, R2.2
TXD: IC1.31, JP1.5
WAKE_HW: IC1.2, R18.2, U1.15
WAKE_SW: IC1.9, R17.2, U1.7

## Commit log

2017-08-17 設計開始
2017-08-17 edit sphere_robo
2017-08-19 ライブラリ追加
2017-08-19 edit gitignore
2017-08-19 edit gitigore
2017-08-19 sphere_robo 試作設計完了
2017-08-26 パラメータ決定
2017-08-27 rev2設計開始
2017-08-27 RN4020_Breakout 設計開始
2017-08-27 touch_controller rev2
2017-08-27 ライブラリ編集
2017-09-21 add library
2017-09-21 hemisphere_robo 設計開始
2017-09-23 設計完了
2017-10-05 抵抗値変更
2017-11-24 drum robo設計開始
2017-11-24 rev2 退避
2017-11-24 rev1退避
2017-11-24 rev3設計開始
2017-11-24 rev3設計完了
